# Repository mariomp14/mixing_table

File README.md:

# mixing_table
 This desing has some errors! If you want do the the project you have to change some things. During the explain the errors will be pointed out and explained. The idea of this project is to develop and build a mixing table with 2 mono input channels to which we can adjust the high and low frequencies, the volume and mix the 2 songs.

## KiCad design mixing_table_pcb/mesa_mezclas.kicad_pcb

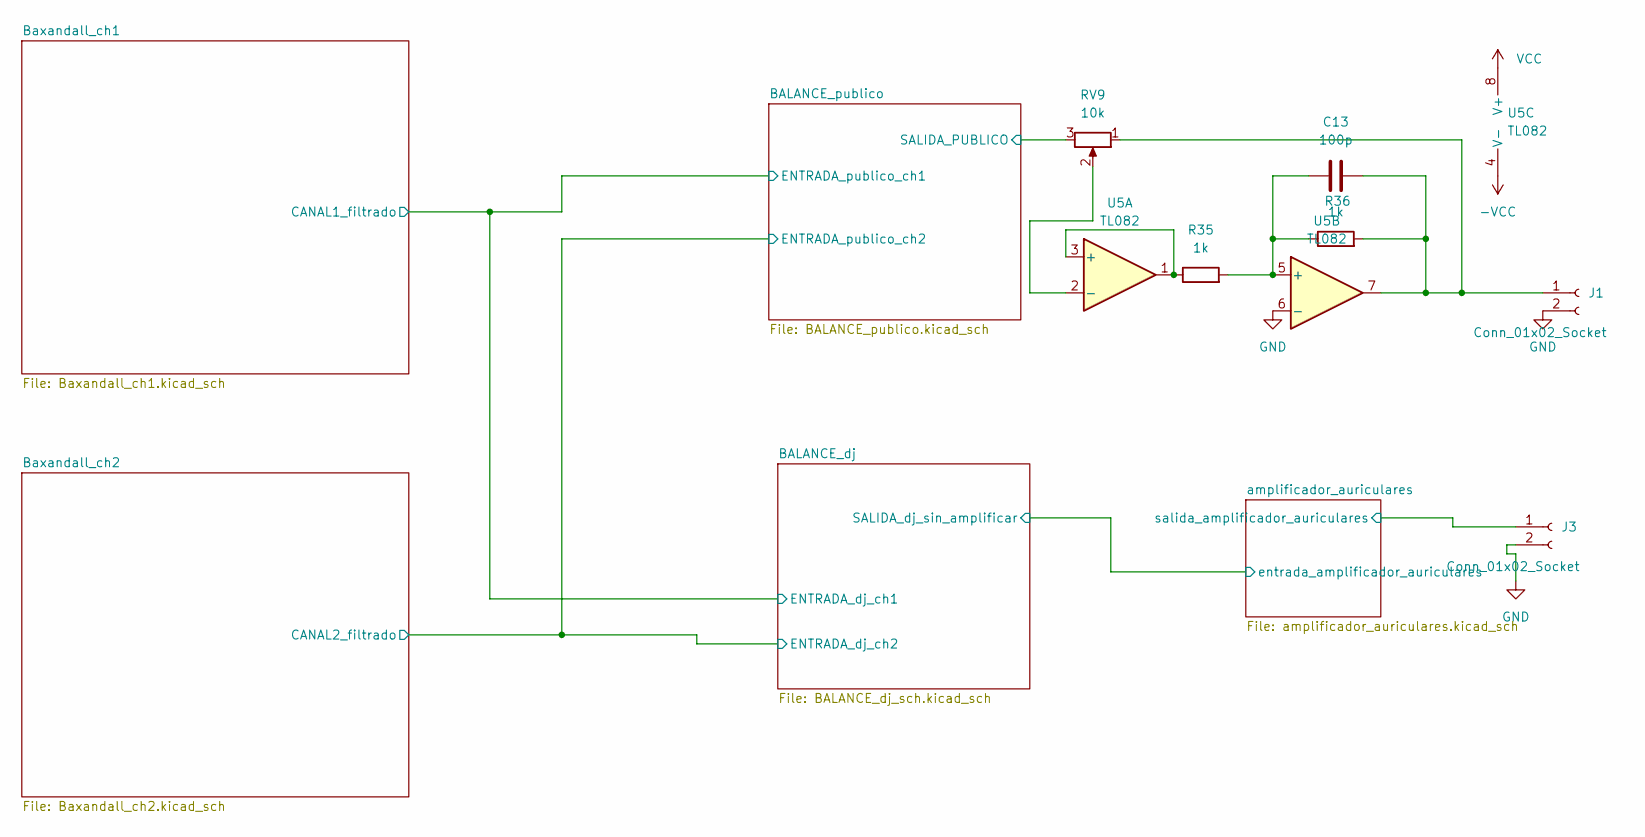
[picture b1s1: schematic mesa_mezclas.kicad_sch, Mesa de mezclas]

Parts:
C13: 100p; C_0805_2012Metric_Pad1.18x1.45mm_HandSolder
J1, J3: Conn_01x02_Socket; PinHeader_1x02_P2.54mm_Vertical
R35, R36: 1k; R_0805_2012Metric_Pad1.20x1.40mm_HandSolder
RV9: 10k; PinHeader_1x03_P2.54mm_Vertical
U5: TL082; SOIC-8_3.9x4.9mm_P1.27mm

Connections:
-VCC: U5.4 (V-); also elsewhere on the board
/BALANCE_publico/SALIDA_PUBLICO: RV9.3; also elsewhere on the board
/amplificador_auriculares/salida_amplificador_auriculares: J3.1; also elsewhere on the board
GND: J1.2, J3.2, U5.6 (-); also elsewhere on the board
unnamed: C13.2, J1.1, R36.2, RV9.1, U5.7
unnamed: R35.1, U5.1, U5.3 (+)
unnamed: RV9.2, U5.2 (-)
unnamed: C13.1, R35.2, R36.1, U5.5 (+)
VCC: U5.8 (V+); also elsewhere on the board

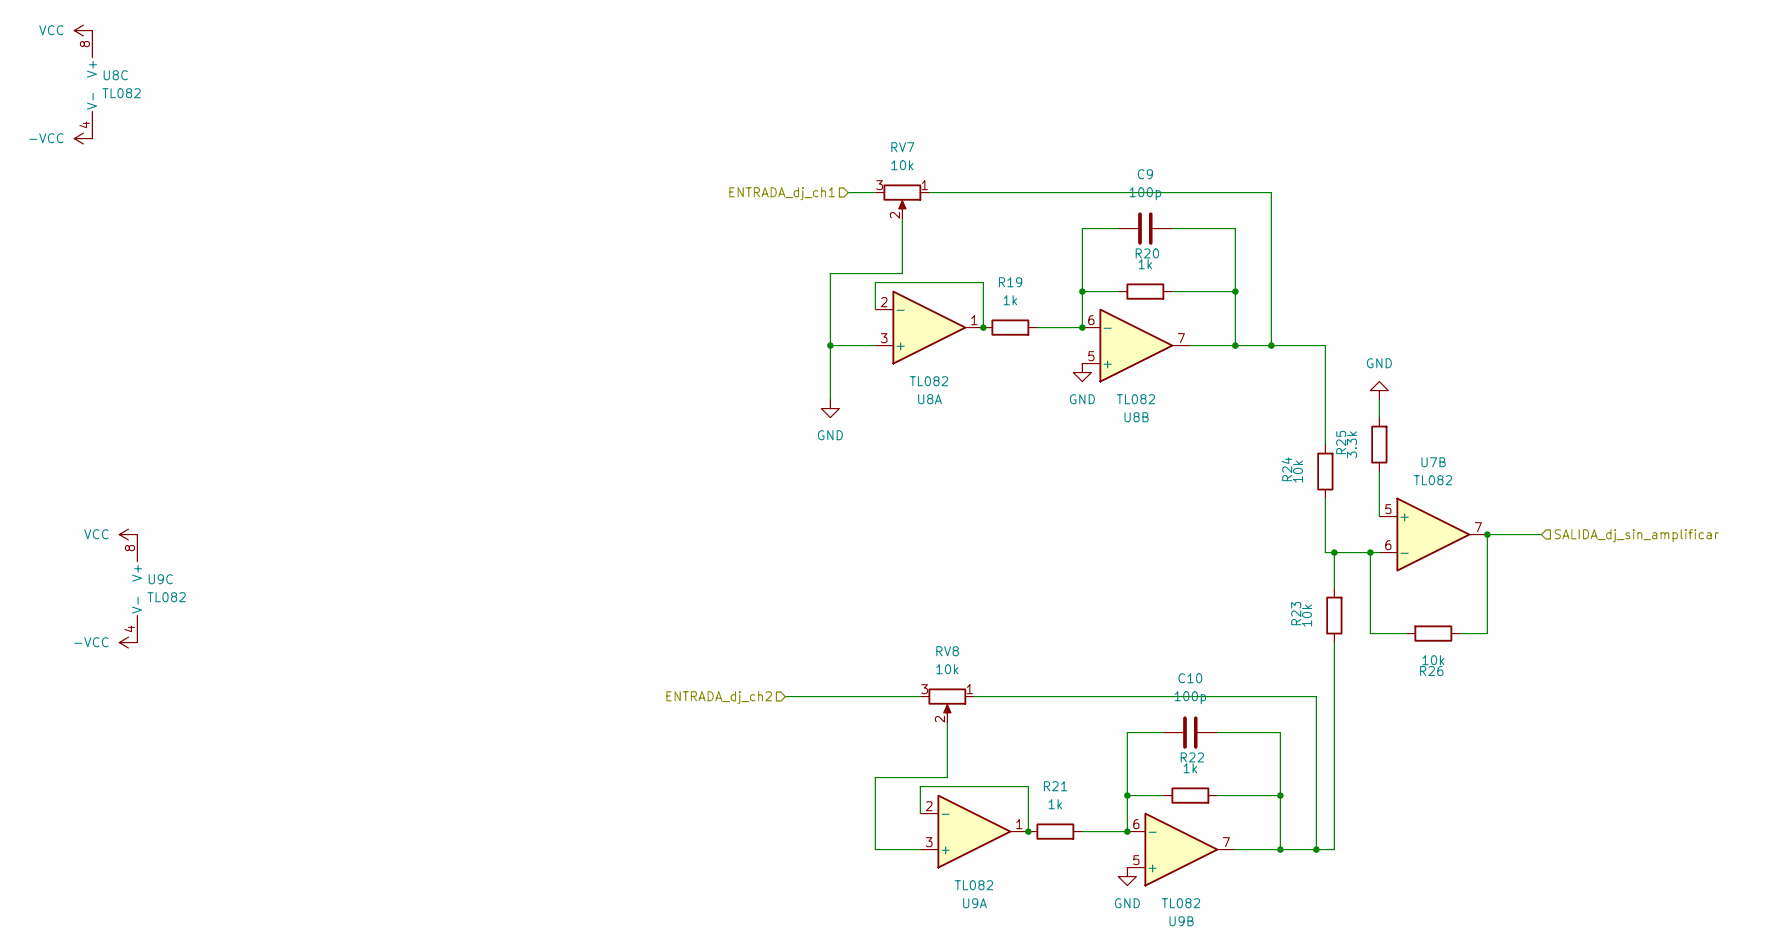
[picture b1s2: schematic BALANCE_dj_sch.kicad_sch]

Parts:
C9, C10: 100p; C_0805_2012Metric_Pad1.18x1.45mm_HandSolder
R19, R20, R21, R22: 1k; R_0805_2012Metric_Pad1.20x1.40mm_HandSolder
R23, R24, R26: 10k; R_0805_2012Metric_Pad1.20x1.40mm_HandSolder
R25: 3.3k; R_0805_2012Metric_Pad1.20x1.40mm_HandSolder
RV7, RV8: 10k; PinHeader_1x03_P2.54mm_Vertical
U7, U8, U9: TL082; SOIC-8_3.9x4.9mm_P1.27mm

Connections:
-VCC: U8.4 (V-), U9.4 (V-); also elsewhere on the board
/BALANCE_dj/ENTRADA_dj_ch1: RV7.3; also elsewhere on the board
/BALANCE_dj/ENTRADA_dj_ch2: RV8.3; also elsewhere on the board
/BALANCE_dj/SALIDA_dj_sin_amplificar: R26.1, U7.7; also elsewhere on the board
GND: R25.2, RV7.2, U8.3 (+), U8.5 (+), U9.5 (+); also elsewhere on the board
unnamed: C9.2, R20.2, R24.2, RV7.1, U8.7
unnamed: C10.2, R22.2, R23.1, RV8.1, U9.7
unnamed: R25.1, U7.5 (+)
unnamed: R23.2, R24.1, R26.2, U7.6 (-)
unnamed: R19.1, U8.1, U8.2 (-)
unnamed: C9.1, R19.2, R20.1, U8.6 (-)
unnamed: RV8.2, U9.3 (+)
unnamed: R21.1, U9.1, U9.2 (-)
unnamed: C10.1, R21.2, R22.1, U9.6 (-)
VCC: U8.8 (V+), U9.8 (V+); also elsewhere on the board

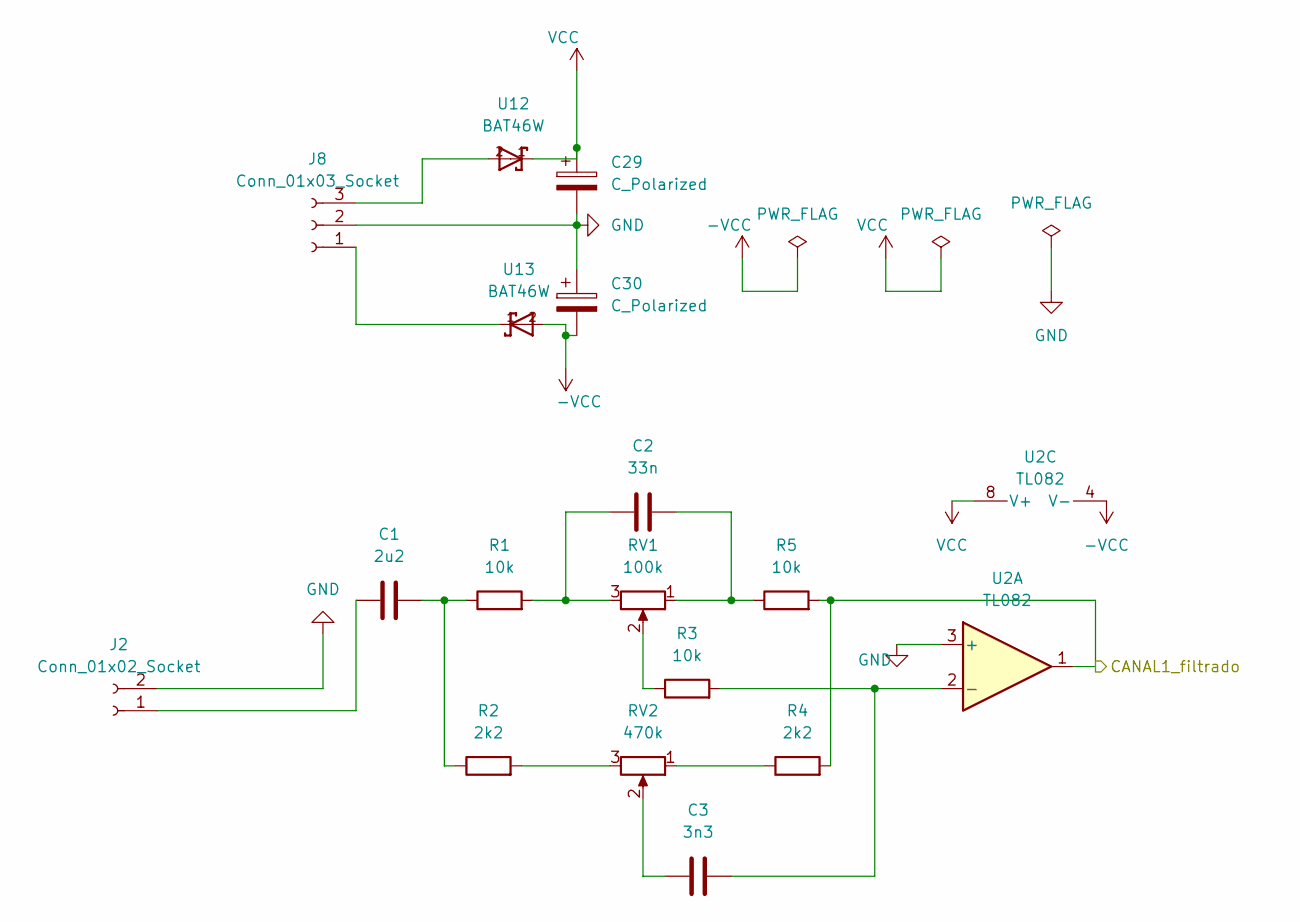
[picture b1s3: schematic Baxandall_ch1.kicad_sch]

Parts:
C1: 2u2; C_0805_2012Metric_Pad1.18x1.45mm_HandSolder
C2: 33n; C_0805_2012Metric_Pad1.18x1.45mm_HandSolder
C3: 3n3; C_0805_2012Metric_Pad1.18x1.45mm_HandSolder
C29, C30: C_Polarized; CP_Elec_5x5.3
J2: Conn_01x02_Socket; PinHeader_1x02_P2.54mm_Vertical
J8: Conn_01x03_Socket; PinHeader_1x03_P2.54mm_Vertical
R1, R3, R5: 10k; R_0805_2012Metric_Pad1.20x1.40mm_HandSolder
R2, R4: 2k2; R_0805_2012Metric_Pad1.20x1.40mm_HandSolder
RV1: 100k; PinHeader_1x03_P2.54mm_Vertical
RV2: 470k; PinHeader_1x03_P2.54mm_Vertical
U2: TL082; SOIC-8_3.9x4.9mm_P1.27mm
U12, U13: BAT46W; D_SOD-123F

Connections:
-VCC: C30.2, U2.4 (V-), U13.2; also elsewhere on the board
/BALANCE_dj/ENTRADA_dj_ch1: R4.2, R5.2, U2.1; also elsewhere on the board
GND: C29.2, C30.1, J2.2, J8.2, U2.3 (+); also elsewhere on the board
unnamed: C1.2, R1.1, R2.1
unnamed: C2.1, R1.2, RV1.3
unnamed: C2.2, R5.1, RV1.1
unnamed: C3.1, RV2.2
unnamed: C1.1, J2.1
unnamed: J8.1, U13.1
unnamed: J8.3, U12.2
unnamed: R2.2, RV2.3
unnamed: R3.1, RV1.2
unnamed: R4.1, RV2.1
unnamed: C3.2, R3.2, U2.2 (-)
VCC: C29.1, U2.8 (V+), U12.1; also elsewhere on the board

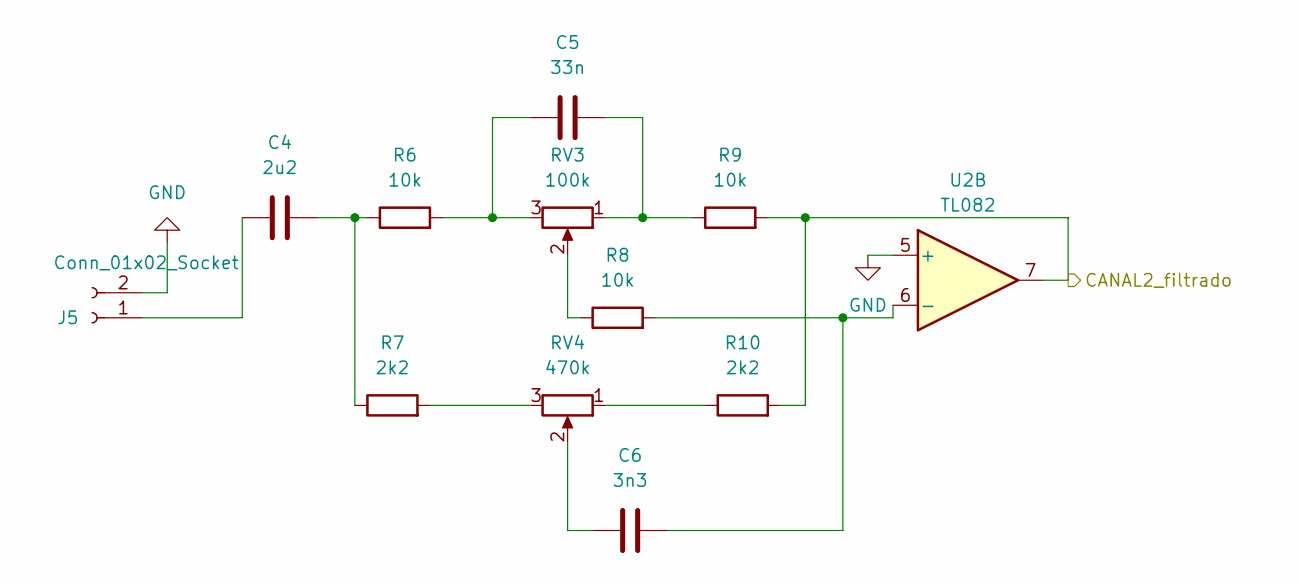
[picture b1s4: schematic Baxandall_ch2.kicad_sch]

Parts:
C4: 2u2; C_0805_2012Metric_Pad1.18x1.45mm_HandSolder
C5: 33n; C_0805_2012Metric_Pad1.18x1.45mm_HandSolder
C6: 3n3; C_0805_2012Metric_Pad1.18x1.45mm_HandSolder
J5: Conn_01x02_Socket; PinHeader_1x02_P2.54mm_Vertical
R6, R8, R9: 10k; R_0805_2012Metric_Pad1.20x1.40mm_HandSolder
R7, R10: 2k2; R_0805_2012Metric_Pad1.20x1.40mm_HandSolder
RV3: 100k; PinHeader_1x03_P2.54mm_Vertical
RV4: 470k; PinHeader_1x03_P2.54mm_Vertical
U2: TL082; SOIC-8_3.9x4.9mm_P1.27mm

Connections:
/BALANCE_dj/ENTRADA_dj_ch2: R9.2, R10.2, U2.7; also elsewhere on the board
GND: J5.2, U2.5 (+); also elsewhere on the board
unnamed: C4.2, R6.1, R7.1
unnamed: C5.1, R6.2, RV3.3
unnamed: C5.2, R9.1, RV3.1
unnamed: C6.1, RV4.2
unnamed: C4.1, J5.1
unnamed: R7.2, RV4.3
unnamed: R8.1, RV3.2
unnamed: R10.1, RV4.1
unnamed: C6.2, R8.2, U2.6 (-)

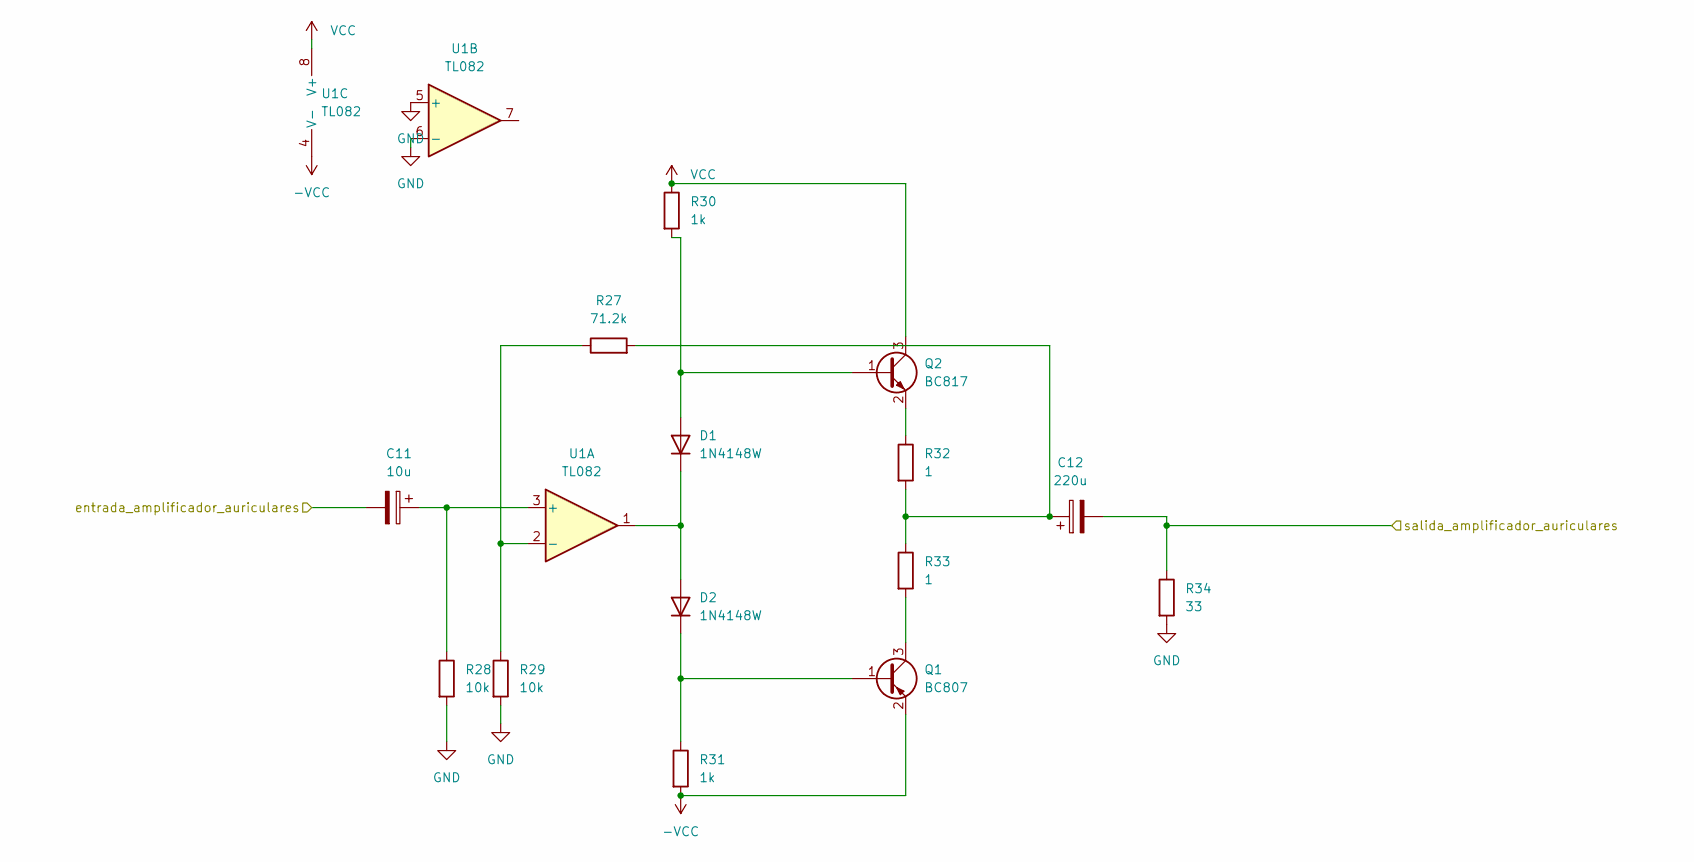
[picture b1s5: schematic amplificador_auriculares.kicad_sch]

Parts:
C11: 10u; CP_Elec_5x5.3
C12: 220u; CP_Elec_5x5.3
D1, D2: 1N4148W; D_SOD-123
Q1: BC807; SOT-23
Q2: BC817; SOT-23
R27: 71.2k; R_0805_2012Metric_Pad1.20x1.40mm_HandSolder
R28, R29: 10k; R_0805_2012Metric_Pad1.20x1.40mm_HandSolder
R30, R31: 1k; R_0805_2012Metric_Pad1.20x1.40mm_HandSolder
R32, R33: 1; R_0805_2012Metric_Pad1.20x1.40mm_HandSolder
R34: 33; R_0805_2012Metric_Pad1.20x1.40mm_HandSolder
U1: TL082; SOIC-8_3.9x4.9mm_P1.27mm

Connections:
-VCC: Q1.2 (E), R31.2, U1.4 (V-); also elsewhere on the board
/BALANCE_dj/SALIDA_dj_sin_amplificar: C11.2; also elsewhere on the board
/amplificador_auriculares/salida_amplificador_auriculares: C12.2, R34.1; also elsewhere on the board
GND: R28.2, R29.2, R34.2, U1.5 (+), U1.6 (-); also elsewhere on the board
unnamed: C12.1, R27.2, R32.2, R33.1
unnamed: D1.2 (A), Q2.1 (B), R30.2
unnamed: D1.1 (K), D2.2 (A), U1.1
unnamed: D2.1 (K), Q1.1 (B), R31.1
unnamed: Q1.3 (C), R33.2
unnamed: Q2.2 (E), R32.1
unnamed: C11.1, R28.1, U1.3 (+)
unnamed: R27.1, R29.1, U1.2 (-)
VCC: Q2.3 (C), R30.1, U1.8 (V+); also elsewhere on the board

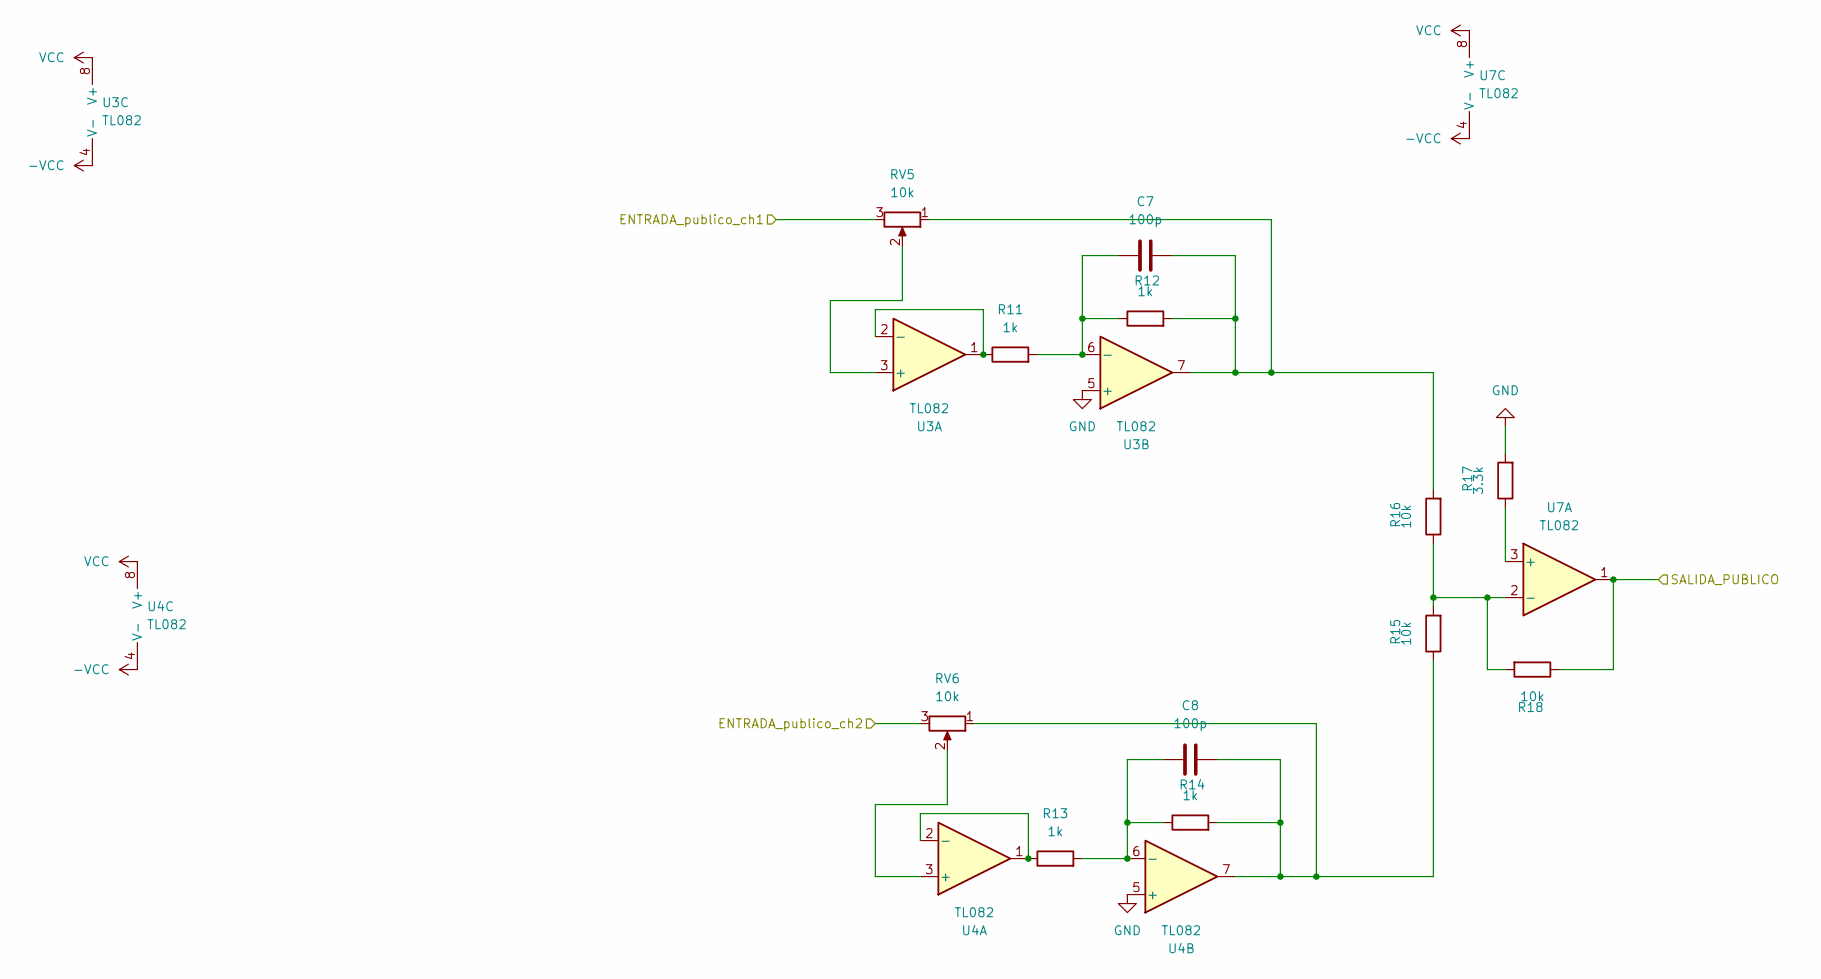
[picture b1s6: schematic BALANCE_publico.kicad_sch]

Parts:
C7, C8: 100p; C_0805_2012Metric_Pad1.18x1.45mm_HandSolder
R11, R12, R13, R14: 1k; R_0805_2012Metric_Pad1.20x1.40mm_HandSolder
R15, R16, R18: 10k; R_0805_2012Metric_Pad1.20x1.40mm_HandSolder
R17: 3.3k; R_0805_2012Metric_Pad1.20x1.40mm_HandSolder
RV5, RV6: 10k; PinHeader_1x03_P2.54mm_Vertical
U3, U4, U7: TL082; SOIC-8_3.9x4.9mm_P1.27mm

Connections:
-VCC: U3.4 (V-), U4.4 (V-), U7.4 (V-); also elsewhere on the board
/BALANCE_dj/ENTRADA_dj_ch1: RV5.3; also elsewhere on the board
/BALANCE_dj/ENTRADA_dj_ch2: RV6.3; also elsewhere on the board
/BALANCE_publico/SALIDA_PUBLICO: R18.1, U7.1; also elsewhere on the board
GND: R17.2, U3.5 (+), U4.5 (+); also elsewhere on the board
unnamed: C7.2, R12.2, R16.2, RV5.1, U3.7
unnamed: C8.2, R14.2, R15.1, RV6.1, U4.7
unnamed: RV5.2, U3.3 (+)
unnamed: R11.1, U3.1, U3.2 (-)
unnamed: C7.1, R11.2, R12.1, U3.6 (-)
unnamed: RV6.2, U4.3 (+)
unnamed: R13.1, U4.1, U4.2 (-)
unnamed: C8.1, R13.2, R14.1, U4.6 (-)
unnamed: R17.1, U7.3 (+)
unnamed: R15.2, R16.1, R18.2, U7.2 (-)
VCC: U3.8 (V+), U4.8 (V+), U7.8 (V+); also elsewhere on the board

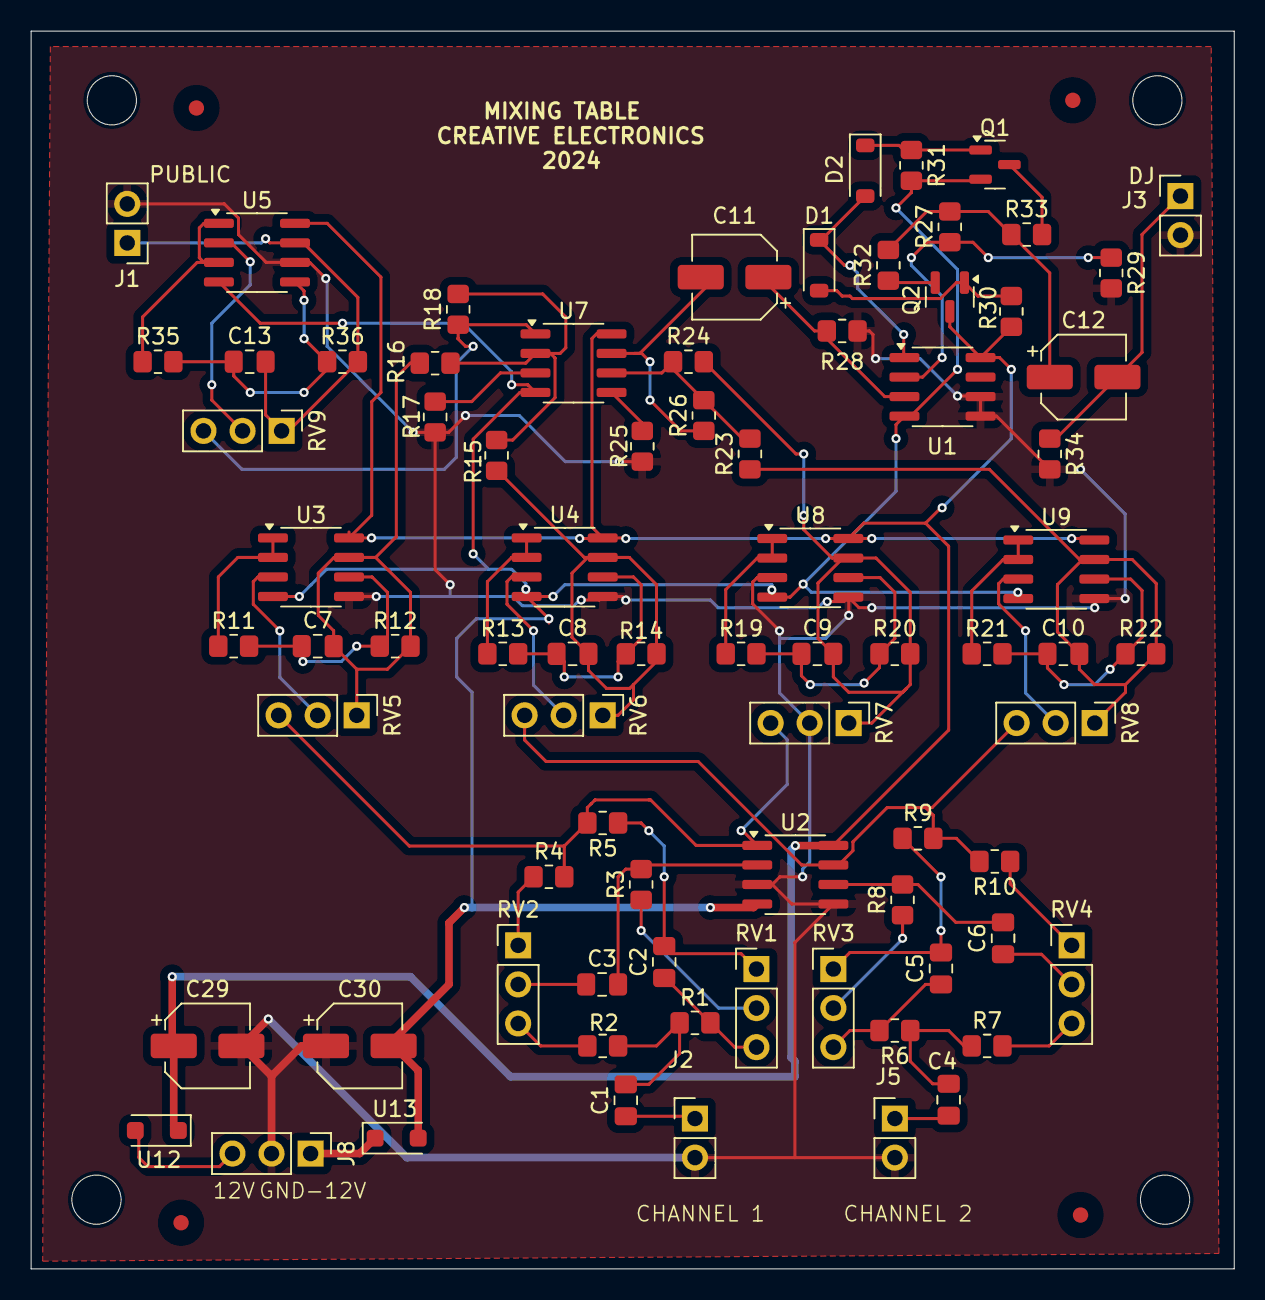
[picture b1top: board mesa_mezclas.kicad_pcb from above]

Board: 2 copper layers, 78.2 x 80.5 mm, 79 parts (0 on the bottom side), 59 nets.

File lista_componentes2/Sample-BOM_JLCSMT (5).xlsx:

Comment | Designator | Footprint
2.2uF | C1,C4 | C_0805_2012Metric_Pad1.18x1.45mm_HandSolder
33nF | C2,C5 | C_0805_2012Metric_Pad1.18x1.45mm_HandSolder
3.3nF | C3,C6 | C_0805_2012Metric_Pad1.18x1.45mm_HandSolder
100pF | C7,C8,C9,C10,C13 | C_0805_2012Metric_Pad1.18x1.45mm_HandSolder
10uF | C11 | CP_Elec_5x5.3
220uF | C12 | CCP_Elec_5x5.3
VE-470M1CTR-0505 | C29,C30 | CP_Elec_5x5.3
1N4148W | D1,D2 | D_SOD-123
1x02 2.54mm Vertical Header | J1,J2,J3,J5 | PinHeader_1x02_P2.54mm_Vertical
1x03 2.54mm Vertical Header | J8 | PinHeader_1x03_P2.54mm_Vertical
BC807 | Q1 | SOT-23
BC817 | Q2 | SOT-23
10k | R1,R3,R5,R6,R8,R9,R15,R16,R18,R23,R24,R26,R28,R29 | R_0805_2012Metric_Pad1.20x1.40mm_HandSolder
2.2k | R2,R4,R7,R10 | R_0805_2012Metric_Pad1.20x1.40mm_HandSolder
1k | R11,R12,R13,R14,R19,R20,R21,R22,R30,R31,R35,R36 | R_0805_2012Metric_Pad1.20x1.40mm_HandSolder
3.3k | R17,R25 | R_0805_2012Metric_Pad1.20x1.40mm_HandSolder
70k | R27 | R_0805_2012Metric_Pad1.20x1.40mm_HandSolder
1 | R32,R33 | R_0805_2012Metric_Pad1.20x1.40mm_HandSolder
33 | R34 | R_0805_2012Metric_Pad1.20x1.40mm_HandSolder
TL082 | U1,U2,U3,U4,U5,U7,U8,U9 | SOIC-8_3.9x4.9mm_P1.27mm
BAT46W | U12,U13 | D_SOD-123F
1x03 2.54mm Vertical Header | RV1,RV3,RV2,RV4,RV5,RV6,RV7,RV8,RV9 | PinHeader_1x03_P2.54mm_Vertical

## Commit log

2025-01-19 version_final(error)
2025-01-19 componentes_placement
